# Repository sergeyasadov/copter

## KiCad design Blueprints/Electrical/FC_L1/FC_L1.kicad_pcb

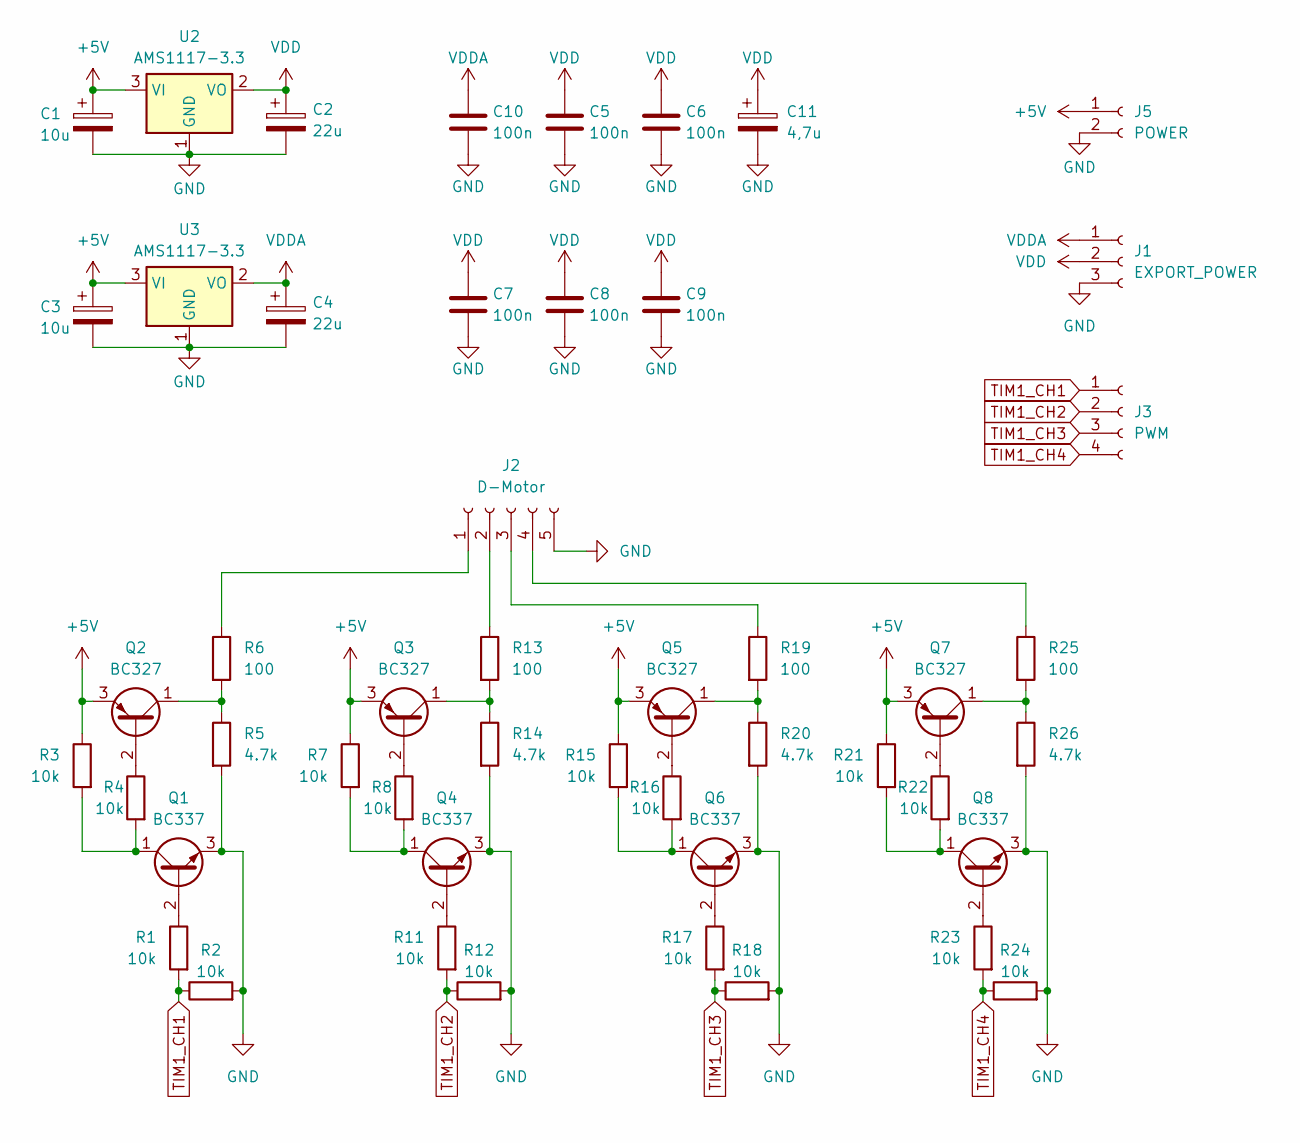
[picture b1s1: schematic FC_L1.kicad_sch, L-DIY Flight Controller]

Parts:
C1, C3: 10u; CP_Radial_D10.0mm_P5.00mm
C2, C4: 22u; CP_Radial_D10.0mm_P5.00mm
C5, C6, C7, C8, C9, C10: 100n; C_Disc_D10.0mm_W2.5mm_P5.00mm
C11: 4,7u; CP_Radial_D10.0mm_P5.00mm
J1: EXPORT_POWER; PinHeader_1x03_P2.00mm_Vertical
J2: D-Motor; PinHeader_1x05_P2.00mm_Vertical
J3: PWM
J5: POWER; PinHeader_1x02_P2.00mm_Vertical
Q1, Q4, Q6, Q8: BC337; TO-92_Inline
Q2, Q3, Q5, Q7: BC327; TO-92_Inline
R1, R2, R3, R4, R7, R8, R11, R12, R15, R16, R17, R18, R21, R22, R23, R24: 10k; R_Axial_DIN0204_L3.6mm_D1.6mm_P1.90mm_Vertical
R5, R14, R20, R26: 4.7k; R_Axial_DIN0204_L3.6mm_D1.6mm_P1.90mm_Vertical
R6, R13, R19, R25: 100; R_Axial_DIN0204_L3.6mm_D1.6mm_P1.90mm_Vertical
U2, U3: AMS1117-3.3; SOT-223-3_TabPin2

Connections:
+5V: C1.1, C3.1, J5.1, Q2.3 (E), Q3.3 (E), Q5.3 (E), Q7.3 (E), R3.1, R7.1, R15.1, R21.1, U2.3 (VI), U3.3 (VI)
GND: C1.2, C2.2, C3.2, C4.2, C5.2, C6.2, C7.2, C8.2, C9.2, C10.2, C11.2, J1.3, J2.5, J5.2, Q1.3 (E), Q4.3 (E), Q6.3 (E), Q8.3 (E), R2.2, R5.2, R12.2, R14.2, R18.2, R20.2, R24.2, R26.2, U2.1 (GND), U3.1 (GND)
unnamed: J2.1, R6.1
unnamed: J2.2, R13.1
unnamed: J2.3, R19.1
unnamed: J2.4, R25.1
unnamed: Q1.2 (B), R1.1
unnamed: Q1.1 (C), R3.2, R4.2
unnamed: Q2.2 (B), R4.1
unnamed: Q2.1 (C), R5.1, R6.2
unnamed: Q3.2 (B), R8.1
unnamed: Q3.1 (C), R13.2, R14.1
unnamed: Q4.2 (B), R11.1
unnamed: Q4.1 (C), R7.2, R8.2
unnamed: Q5.2 (B), R16.1
unnamed: Q5.1 (C), R19.2, R20.1
unnamed: Q6.2 (B), R17.1
unnamed: Q6.1 (C), R15.2, R16.2
unnamed: Q7.2 (B), R22.1
unnamed: Q7.1 (C), R25.2, R26.1
unnamed: Q8.2 (B), R23.1
unnamed: Q8.1 (C), R21.2, R22.2
TIM1_CH1: J3.1, R1.2, R2.1
TIM1_CH2: J3.2, R11.2, R12.1
TIM1_CH3: J3.3, R17.2, R18.1
TIM1_CH4: J3.4, R23.2, R24.1
VDD: C2.1, C5.1, C6.1, C7.1, C8.1, C9.1, C11.1, J1.2, U2.2 (VO)
VDDA: C4.1, C10.1, J1.1, U3.2 (VO)

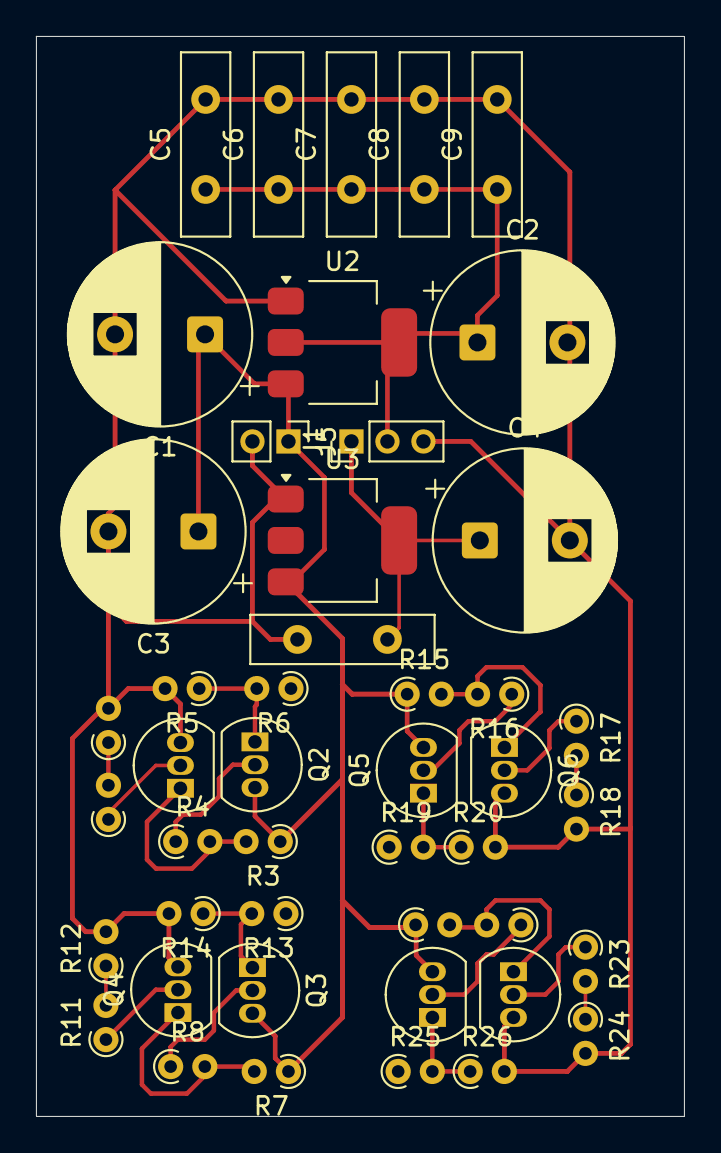
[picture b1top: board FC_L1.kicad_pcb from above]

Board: 2 copper layers, 36.0 x 60.0 mm, 46 parts (0 on the bottom side), 24 nets.

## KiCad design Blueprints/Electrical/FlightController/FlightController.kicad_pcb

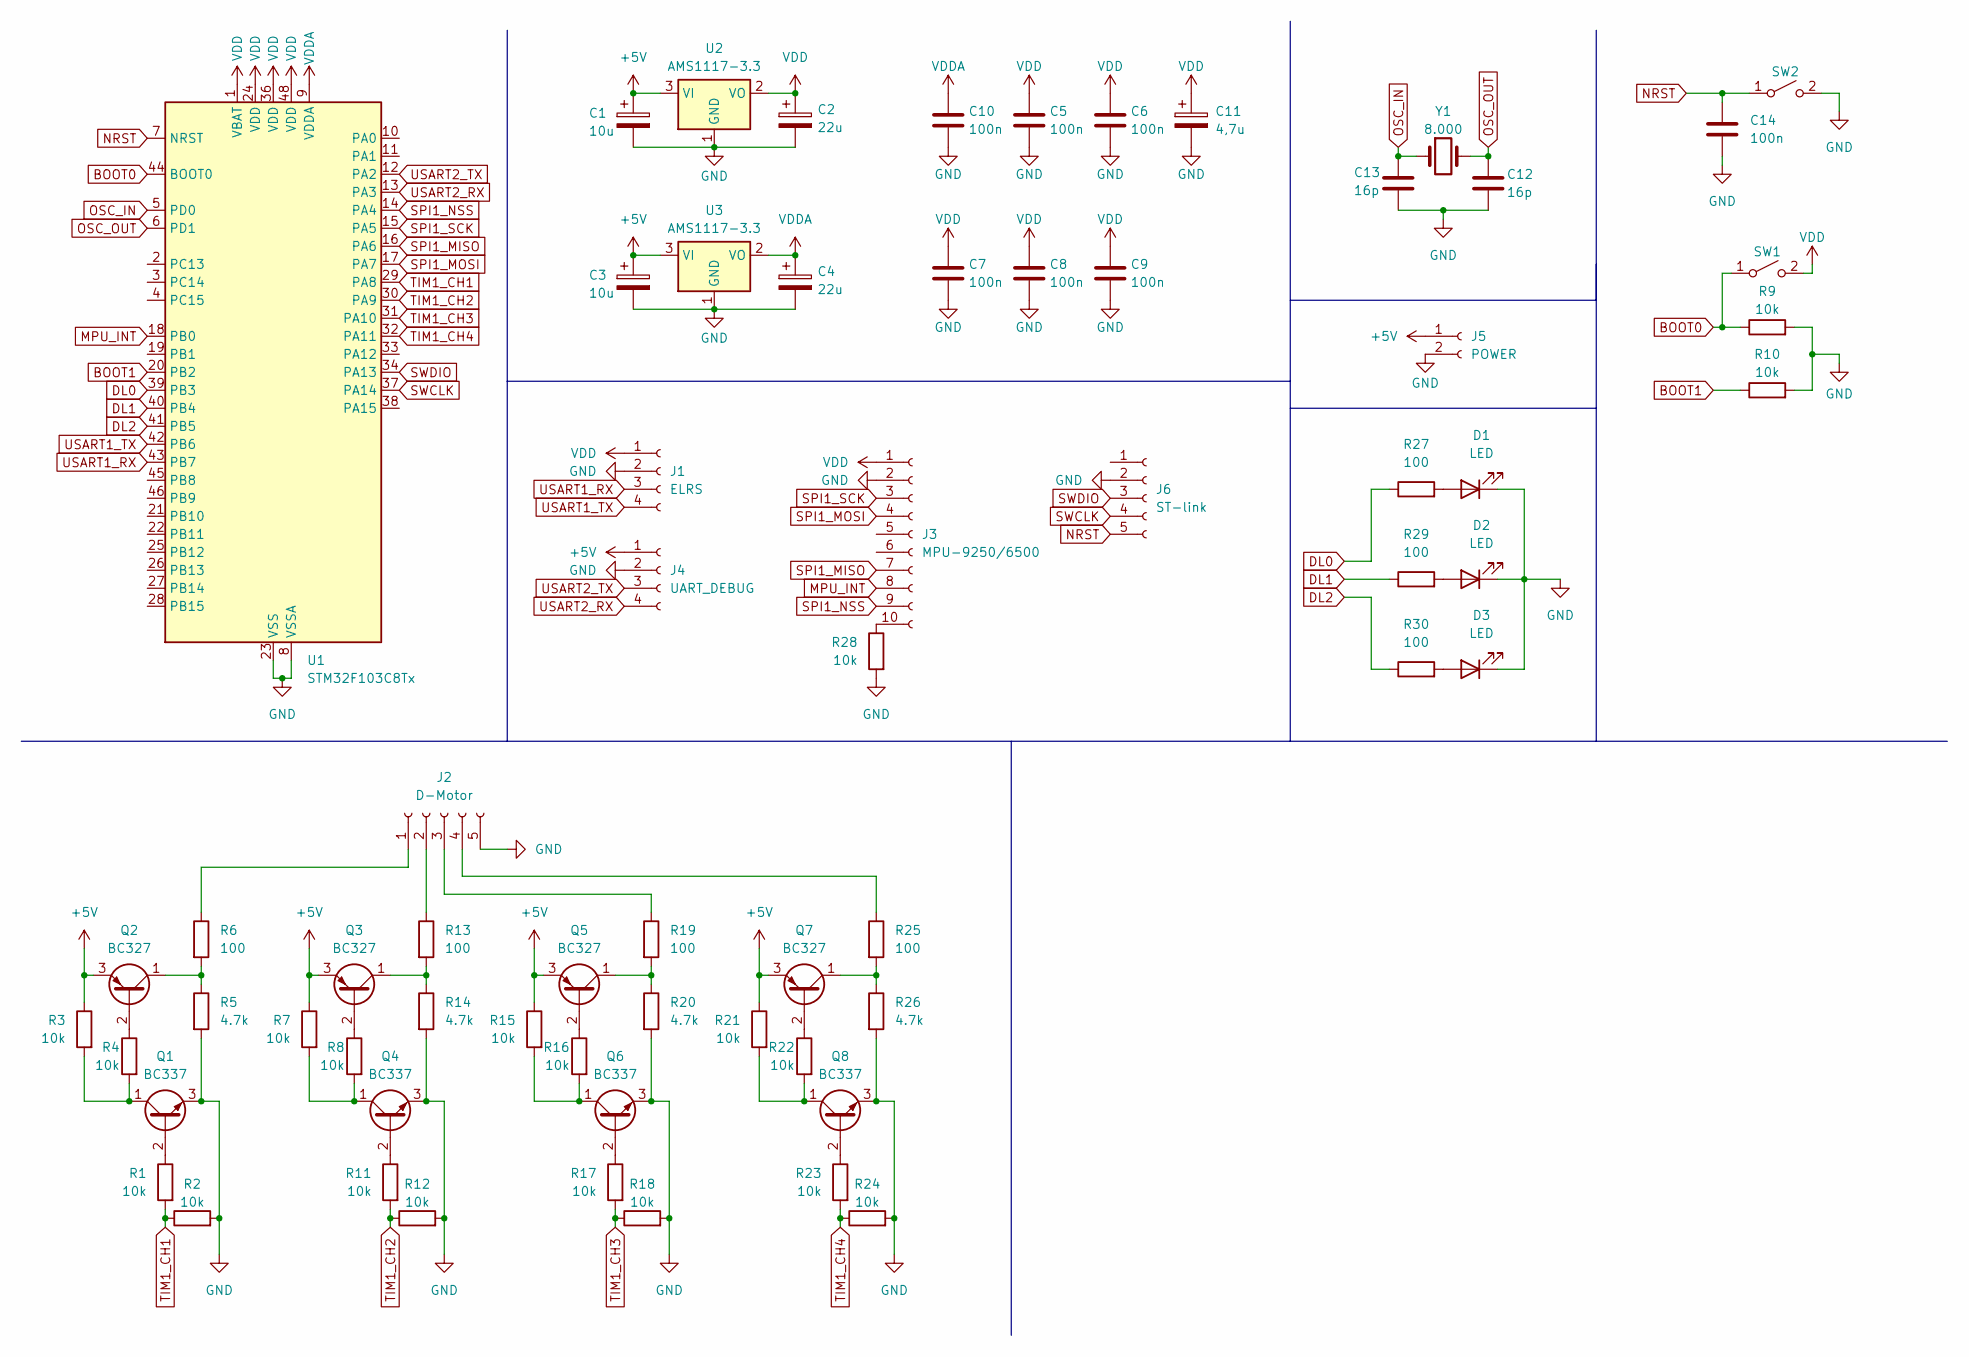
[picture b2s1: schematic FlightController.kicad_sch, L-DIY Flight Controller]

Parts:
C1, C3: 10u; CP_Radial_D10.0mm_P5.00mm
C2, C4: 22u; CP_Radial_D10.0mm_P5.00mm
C5, C6, C7, C8, C9, C10, C14: 100n; C_Disc_D10.0mm_W2.5mm_P5.00mm
C11: 4,7u; CP_Radial_D10.0mm_P5.00mm
C12, C13: 16p; C_Disc_D10.0mm_W2.5mm_P5.00mm
D1, D2, D3: LED; LED_D10.0mm
J1: ELRS; PinHeader_1x04_P2.00mm_Vertical
J2: D-Motor; PinHeader_1x05_P2.00mm_Vertical
J3: MPU-9250/6500; PinHeader_1x10_P2.00mm_Vertical
J4: UART_DEBUG; PinHeader_1x04_P2.00mm_Vertical
J5: POWER; PinHeader_1x02_P2.00mm_Vertical
J6: ST-link; PinHeader_1x05_P2.00mm_Vertical
Q1, Q4, Q6, Q8: BC337; TO-92_Inline
Q2, Q3, Q5, Q7: BC327; TO-92_Inline
R1, R2, R3, R4, R7, R8, R9, R10, R11, R12, R15, R16, R17, R18, R21, R22, R23, R24, R28: 10k; R_Axial_DIN0204_L3.6mm_D1.6mm_P1.90mm_Vertical
R5, R14, R20, R26: 4.7k; R_Axial_DIN0204_L3.6mm_D1.6mm_P1.90mm_Vertical
R6, R13, R19, R25, R27, R29, R30: 100; R_Axial_DIN0204_L3.6mm_D1.6mm_P1.90mm_Vertical
SW1, SW2: SW_SPST; SW_SPST_CK_RS282G05A3
U1: STM32F103C8Tx; LQFP-48_7x7mm_P0.5mm
U2, U3: AMS1117-3.3; SOT-223-3_TabPin2
Y1: 8.000; Crystal_HC49-4H_Vertical

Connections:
+5V: C1.1, C3.1, J4.1, J5.1, Q2.3 (E), Q3.3 (E), Q5.3 (E), Q7.3 (E), R3.1, R7.1, R15.1, R21.1, U2.3 (VI), U3.3 (VI)
BOOT0: R9.1, SW1.1 (A), U1.44 (BOOT0)
BOOT1: R10.1, U1.20 (PB2)
DL0: R27.1, U1.39 (PB3)
DL1: R29.1, U1.40 (PB4)
DL2: R30.1, U1.41 (PB5)
GND: C1.2, C2.2, C3.2, C4.2, C5.2, C6.2, C7.2, C8.2, C9.2, C10.2, C11.2, C12.2, C13.2, C14.2, D1.1 (K), D2.1 (K), D3.1 (K), J1.2, J2.5, J3.2, J4.2, J5.2, J6.2, Q1.3 (E), Q4.3 (E), Q6.3 (E), Q8.3 (E), R2.2, R5.2, R9.2, R10.2, R12.2, R14.2, R18.2, R20.2, R24.2, R26.2, R28.2, SW2.2 (B), U1.8 (VSSA), U1.23 (VSS), U1.35 (VSS), U1.47 (VSS), U2.1 (GND), U3.1 (GND)
MPU_INT: J3.8, U1.18 (PB0)
NRST: C14.1, J6.5, SW2.1 (A), U1.7 (NRST)
unnamed: D1.2 (A), R27.2
unnamed: D2.2 (A), R29.2
unnamed: D3.2 (A), R30.2
unnamed: J2.1, R6.1
unnamed: J2.2, R13.1
unnamed: J2.3, R19.1
unnamed: J2.4, R25.1
unnamed: J3.10, R28.1
unnamed: Q1.2 (B), R1.1
unnamed: Q1.1 (C), R3.2, R4.2
unnamed: Q2.2 (B), R4.1
unnamed: Q2.1 (C), R5.1, R6.2
unnamed: Q3.2 (B), R8.1
unnamed: Q3.1 (C), R13.2, R14.1
unnamed: Q4.2 (B), R11.1
unnamed: Q4.1 (C), R7.2, R8.2
unnamed: Q5.2 (B), R16.1
unnamed: Q5.1 (C), R19.2, R20.1
unnamed: Q6.2 (B), R17.1
unnamed: Q6.1 (C), R15.2, R16.2
unnamed: Q7.2 (B), R22.1
unnamed: Q7.1 (C), R25.2, R26.1
unnamed: Q8.2 (B), R23.1
unnamed: Q8.1 (C), R21.2, R22.2
OSC_IN: C13.1, U1.5 (PD0), Y1.1
OSC_OUT: C12.1, U1.6 (PD1), Y1.2
SPI1_MISO: J3.7, U1.16 (PA6)
SPI1_MOSI: J3.4, U1.17 (PA7)
SPI1_NSS: J3.9, U1.14 (PA4)
SPI1_SCK: J3.3, U1.15 (PA5)
SWCLK: J6.4, U1.37 (PA14)
SWDIO: J6.3, U1.34 (PA13)
TIM1_CH1: R1.2, R2.1, U1.29 (PA8)
TIM1_CH2: R11.2, R12.1, U1.30 (PA9)
TIM1_CH3: R17.2, R18.1, U1.31 (PA10)
TIM1_CH4: R23.2, R24.1, U1.32 (PA11)
USART1_RX: J1.3, U1.43 (PB7)
USART1_TX: J1.4, U1.42 (PB6)
USART2_RX: J4.4, U1.13 (PA3)
USART2_TX: J4.3, U1.12 (PA2)
VDD: C2.1, C5.1, C6.1, C7.1, C8.1, C9.1, C11.1, J1.1, J3.1, SW1.2 (B), U1.1 (VBAT), U1.24 (VDD), U1.36 (VDD), U1.48 (VDD), U2.2 (VO)
VDDA: C4.1, C10.1, U1.9 (VDDA), U3.2 (VO)

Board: 2 copper layers, 67 parts (0 on the bottom side), 51 nets, no tracks yet.

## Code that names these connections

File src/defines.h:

#ifndef DEFINES_H
#define DEFINES_H

#include <stm32f1xx.h>

//========================================================================================
#define ARR_SIZE(__arr) (sizeof(__arr) / sizeof(__arr[0]))
//========================================================================================
#define CLAMP(__val, __min, __max) \
    ((__val) < (__min) ? (__min) : (__val) > (__max) ? (__max) : (__val) )
//========================================================================================
#define ARR_FOREACH(__arr, __i) \
    for(uint_fast8_t __i = 0, __s = ARR_SIZE(__arr); __i < __s; __i++)
//========================================================================================
#define LINTERP(x, x1, x2, y1, y2) \
    ( (y1) + ( (uint32_t)((x) - (x1)) * ((y2) - (y1)) ) / ((x2) - (x1)) )
//========================================================================================
#define TICKS_TO_US(x)  (((x) - 992) * 5 / 8 + 1500)
#define US_TO_TICKS(x)  (((x) - 1500) * 8 / 5 + 992)
//========================================================================================
// DEBUG LED
#define DL0_POWER       8UL //PB8
#define DL1_SIGNAL      9UL //PB9
#define DL2_EXCEPTION   5UL //PB5
//========================================================================================
// D-Motor
#define MOTOR_CH1   8UL
#define MOTOR_CH2   9UL
#define MOTOR_CH3   10UL
#define MOTOR_CH4   11UL
//========================================================================================
// ELRS [CRSF] (UART1) [Not sync]
// Async 420'000 bits/s ~ 420'000 baud
// 8 bits, no parity, 1 stop bit
// Interrupt-driven
#define ELRS_TX     6UL //PB6
#define ELRS_RX     7UL //PB7
//========================================================================================
// MPU-9560/6500 (SPI1)
#define MPU_SCK     5UL //PA5
#define MPU_MOSI    7UL //PA7
#define MPU_MISO    6UL //PA6
#define MPU_NSS     4UL //PA4
#define MPU_INT     0UL //PB0
//========================================================================================
// UART_DEBUG (UART2) [Not sync]
#define UART_DEBUG_TX   2u //PA2
#define UART_DEBUG_RX   3u //PA3
//========================================================================================


#endif // DEFINES_H

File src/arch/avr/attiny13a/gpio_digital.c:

#include "gpio.h"

#define __sbi(_Reg, _Port) ((_Reg) |= (1 << (_Port)))
#define __cbi(_Reg, _Port) ((_Reg) &= ~(1 << (_Port))) 


uint8_t GPIO_PIN_0 = PB0;
uint8_t GPIO_PIN_1 = PB1;
uint8_t GPIO_PIN_2 = PB2;
uint8_t GPIO_PIN_3 = PB3;
uint8_t GPIO_PIN_4 = PB4;
uint8_t GPIO_PIN_5 = PB5;


void GPIO_Digital_Init(GPIO_Digital* gpio) {
    GPIO_Digital_SetDir(gpio);
    GPIO_Digital_Set(gpio);
}


void GPIO_Digital_Set(GPIO_Digital* gpio) {
    if(gpio->value) {
        __sbi(PORTB, gpio->pin);
    }
    else {
        __cbi(PORTB, gpio->pin);
    }
}


uint_fast8_t GPIO_Digital_Read(GPIO_Digital* gpio) {
    return PINB & _BV(gpio->pin);
}


void GPIO_Digital_SetDir(GPIO_Digital* gpio) {
    if(gpio->dir == GPIO_DIR__OUTPUT) {
        __sbi(DDRB, gpio->pin);
    }
    else {
        __cbi(DDRB, gpio->pin);
    }
}

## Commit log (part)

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2026-04-11 init
2026-04-13 upd gpio_digital
2026-04-13 upd gpio
2026-04-15 added t44a & CAD blueprint
2026-04-15 upd driver
2026-04-19 upd test
2026-04-27 upd pwm
2026-04-28 upd uart & adc added CAD body
2026-05-02 added TWI
2026-05-03 TWI upd
2026-05-07 to branch ATtiny44A
2026-06-25 added SBUS protocol
2026-06-25 small fix
2026-06-28 upd SBUS protocol
